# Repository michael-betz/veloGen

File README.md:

# light branch
  * No OLED display support
  * No touch button support
  * velogen PCB is in a waterproof box
  - [ ] Support for RGB LED back-light
  - [ ] Support for GPS module
  - [ ] Support for remote server

# veloGen
Minimalist bike computer and hub dynamo power manager.

A typical hub dynamo can deliver approx. 6 - 10 V at 0.5 A. Output current is inductively limited and stays relatively stable over speed. However voltage will go up. A custom made buck converter is used to extract maximum power and charge a 18650 liion cell. The front and back bike lights will be powered by this cell.

Speed and distance is tracked by measuring the zero crossings of the hub dynamo AC output. Data is collected in the CPU until read out by a mobile device over bluetooth and possibly published to a cloud service.

# Brainstorming

 * Will use ESP-WROOM-32 and make good use of the sleep modes
 * AC input zero crossing --> falling edge interrupt. Wake up CPU and increment counting reg.
 * Every second, keep track of:
   * Battery voltage. --> ADC + voltage divider to 3 V
   * Generator RMS(or peak) voltage. --> ADC + voltage divider to 3 V
   * Generator RMS current. --> 5 mOhm shunt + TS1101 + ADC 1 V
   * Battery current in and out --> 5 mOhm shunt + TS1101 + ADC 1 V
   * Realtime clock timestamp
* Store these datasets in a circular buffer in memory, until read out over BLE.
* Manage the Buck converter PWM to charge the battery with maximum current

## PCB

 * 3.3 V LDO
 * WROOM-32
 * Buck inductor
 * Buck Schottky: STPS3L40UF
 * High side mosfet driver: LTC4440-5 in SOT-23
 * High side Mosfet: STL6N3LLH6
 * 4 x schottky diode for bridge rectifier
 * Smoothing cap (10 uF?)
 * 2 x current sensing shunt (Igenerator, Ibattery) + 2 x TS1101
 * IN system programming pins
 * P - channel mosfet to switch off external power on fault (low battery / overcurrent)

### Datasheets
 * [MCP1630](http://ww1.microchip.com/downloads/en/DeviceDoc/21896b.pdf)
 * [LiIon app note](http://ww1.microchip.com/downloads/en/DeviceDoc/51555b.pdf)

## 3D printed case

 * Mounts with zip ties / verlcro straps on the frame between 2 tubes angeled at 120 deg
 * 2 Shellswhich clip / screw together
 * 5 mm wall thickness with a groove to place an O-ring between the shells
 * AC input cable (2 pin)
 * DC output + I2C cable (4 pin)

# Rev1 Notes
  * Need mounting holes on PCB
  * Case clamping the PCB doesn't work like that
  * Case make teeth tighter
  * Need to find less huge connectors for battery, dynamo and I2C
  * Add OLED to case (Case and PCB can be made wider)

# Bringup (rev1)
  * connect pogo pin adapter to board and USB serial cable
  * force flash voltage to 3.3V

```bash
$ espefuse.py set_flash_voltage 3.3V
espefuse.py v2.7
Connecting........_____....._
Enable internal flash voltage regulator (VDD_SDIO) to 3.3V.
The following efuses are burned: XPD_SDIO_FORCE, XPD_SDIO_REG, XPD_SDIO_TIEH.
This is an irreversible operation.
Type 'BURN' (all capitals) to continue.
BURN
VDD_SDIO setting complete.

$ esptool.py flash_id
esptool.py v2.7
Found 1 serial ports
Serial port /dev/ttyUSB0
Connecting........__
Detecting chip type... ESP32
Chip is ESP32D0WDQ5 (revision 1)
Features: WiFi, BT, Dual Core, 240MHz, VRef calibration in efuse, Coding Scheme None
Crystal is 40MHz
MAC: 40:f5:20:5c:8d:48
Uploading stub...
Running stub...
Stub running...
Manufacturer: c8
Device: 4018
Detected flash size: 16MB
Hard resetting via RTS pin..
```

  * `pio run -t uploadfs`
  * `pio run -t upload -t monitor`

You should see velogen booting up in the terminal.

# Changes to add for REV2

  * add 200k pulldown and 10 nF RC filter to speed sense pin
  * add Zener diode across supply rail
  * real buttons
  * better connectors (waterproofing)
  * Switchable battery power output for front light?
  * Switchable 5 V output for WS2812

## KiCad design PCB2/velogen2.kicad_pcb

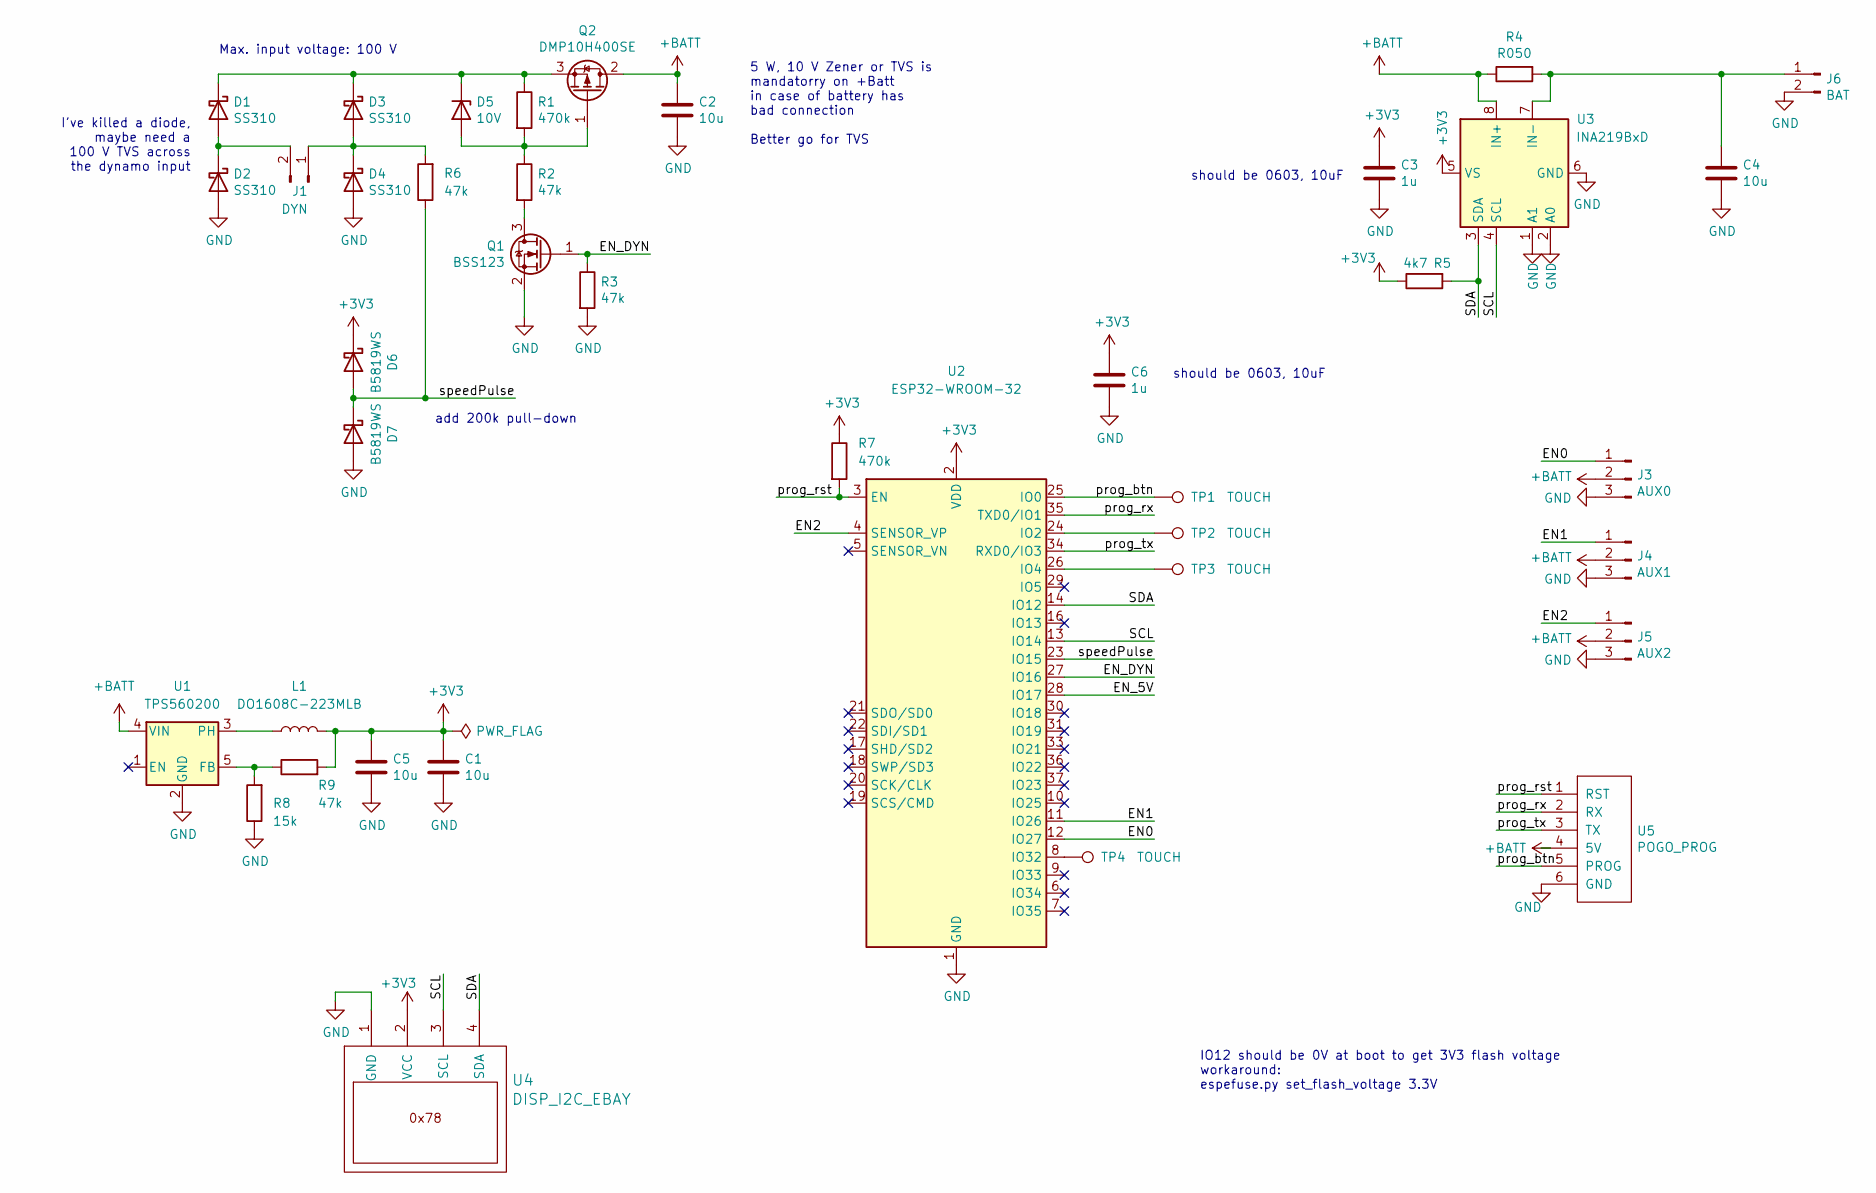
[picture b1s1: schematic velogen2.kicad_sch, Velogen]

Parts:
C1, C5: 10u; C_0603_1608Metric
C2, C4: 10u; C_1210_3225Metric
C3, C6: 1u; C_0805_2012Metric
D1, D2, D3, D4: SS310; D_SMA
D5: 10V; D_SOD-123
D6, D7: B5819WS; D_SOD-323
J1: DYN; JST_XH_S2B-XH-A-1_1x02_P2.50mm_Horizontal
J3: AUX0; JST_XH_S3B-XH-A-1_1x03_P2.50mm_Horizontal
J4: AUX1; JST_XH_S3B-XH-A-1_1x03_P2.50mm_Horizontal
J5: AUX2; JST_XH_S3B-XH-A-1_1x03_P2.50mm_Horizontal
J6: BAT; JST_XH_S2B-XH-A-1_1x02_P2.50mm_Horizontal
L1: DO1608C-223MLB; DO1608
Q1: BSS123; SOT-23
Q2: DMP10H400SE; SOT-223-3_TabPin2
R1, R7: 470k; R_0805_2012Metric
R2, R3, R6, R9: 47k; R_0805_2012Metric
R4: R050; R_1206_3216Metric
R5: 4k7; R_0805_2012Metric
R8: 15k; R_0805_2012Metric
TP1, TP2, TP3, TP4: TOUCH; TestPoint_THTPad_D1.5mm_Drill0.7mm
U1: TPS560200; SOT-23-5
U2: ESP32-WROOM-32
U3: INA219BxD; SOIC-8_3.9x4.9mm_P1.27mm
U4: DISP_I2C_EBAY
U5: POGO_PROG; myPogoPads

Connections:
+3V3: C1.1, C3.1, C5.1, C6.1, D6.1 (K), L1.2, R5.1, R7.1, R9.2, U2.2 (VDD), U3.5 (VS), U4.2 (VCC)
+BATT: C2.1, J3.2, J4.2, J5.2, Q2.2 (D), R4.1, U1.4 (VIN), U3.8 (IN+), U5.4 (5V)
/EN0: J3.1, U2.12 (IO27)
/EN1: J4.1, U2.11 (IO26)
/EN2: J5.1, U2.4 (SENSOR_VP)
/EN_DYN: Q1.1 (G), R3.1, U2.27 (IO16)
/SCL: U2.13 (IO14), U3.4 (SCL), U4.3 (SCL)
/SDA: R5.2, U2.14 (IO12), U3.3 (SDA), U4.4 (SDA)
/prog_btn: TP1.1, U2.25 (IO0), U5.5 (PROG)
/prog_rst: R7.2, U2.3 (EN), U5.1 (RST)
/prog_rx: U2.35 (TXD0/IO1), U5.2 (RX)
/prog_tx: U2.34 (RXD0/IO3), U5.3 (TX)
/speedPulse: D6.2 (A), D7.1 (K), R6.1, U2.23 (IO15)
GND: C1.2, C2.2, C3.2, C4.2, C5.2, C6.2, D2.2 (A), D4.2 (A), D7.2 (A), J3.3, J4.3, J5.3, J6.2, Q1.2 (S), R3.2, R8.1, U1.2 (GND), U2.1 (GND), U2.15 (GND), U2.38 (GND), U2.39 (GND), U3.1 (A1), U3.2 (A0), U3.6 (GND), U4.1 (GND), U5.6 (GND)
unnamed: C4.1, J6.1, R4.2, U3.7 (IN-)
unnamed: D1.1 (K), D3.1 (K), D5.1 (K), Q2.3 (S), R1.1
unnamed: D1.2 (A), D2.1 (K), J1.2
unnamed: D3.2 (A), D4.1 (K), J1.1, R6.2
unnamed: D5.2 (A), Q2.1 (G), R1.2, R2.1
unnamed: L1.1, U1.3 (PH)
unnamed: Q1.3 (D), R2.2
unnamed: R8.2, R9.1, U1.5 (FB)
unnamed: TP2.1, U2.24 (IO2)
unnamed: TP3.1, U2.26 (IO4)
unnamed: TP4.1, U2.8 (IO32)

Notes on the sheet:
IO12 should be 0V at boot to get 3V3 flash voltage workaround: espefuse.py set_flash_voltage 3.3V
add 200k pull-down
5 W, 10 V Zener or TVS is mandatorry on +Batt in case of battery has bad connection Better go for TVS
should be 0603, 10uF
I've killed a diode, maybe need a 100 V TVS across the dynamo input
Max. input voltage: 100 V

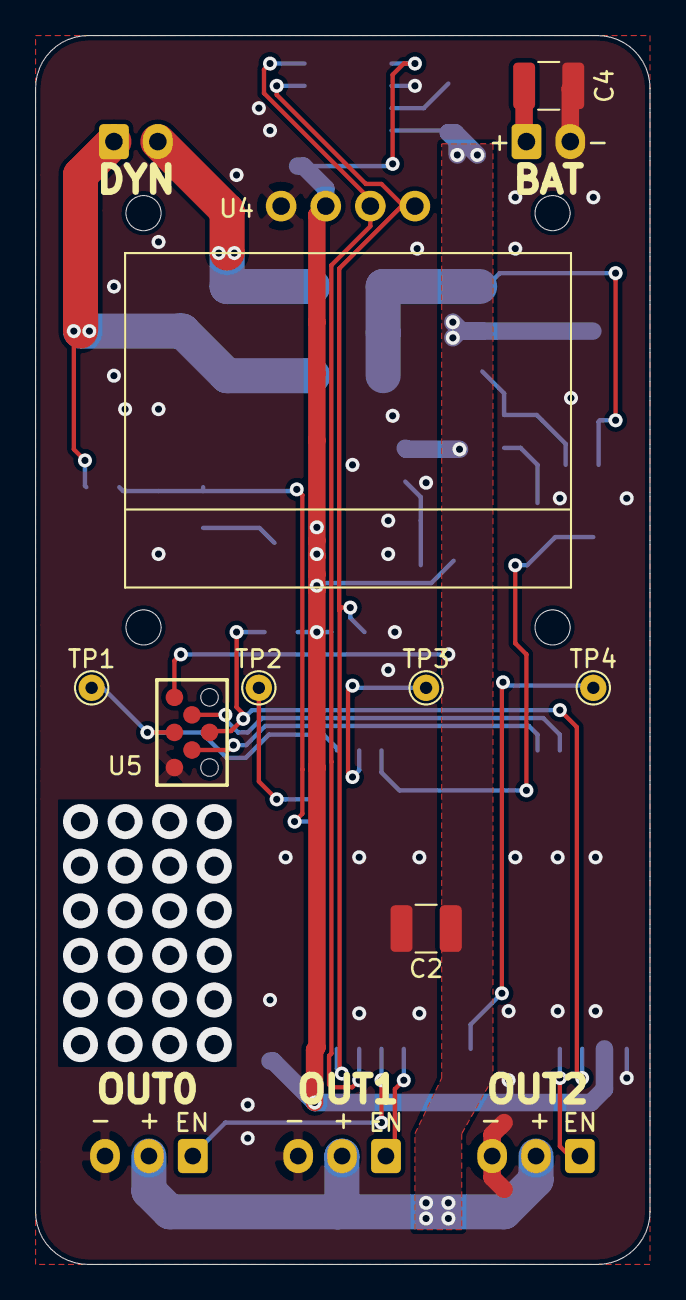
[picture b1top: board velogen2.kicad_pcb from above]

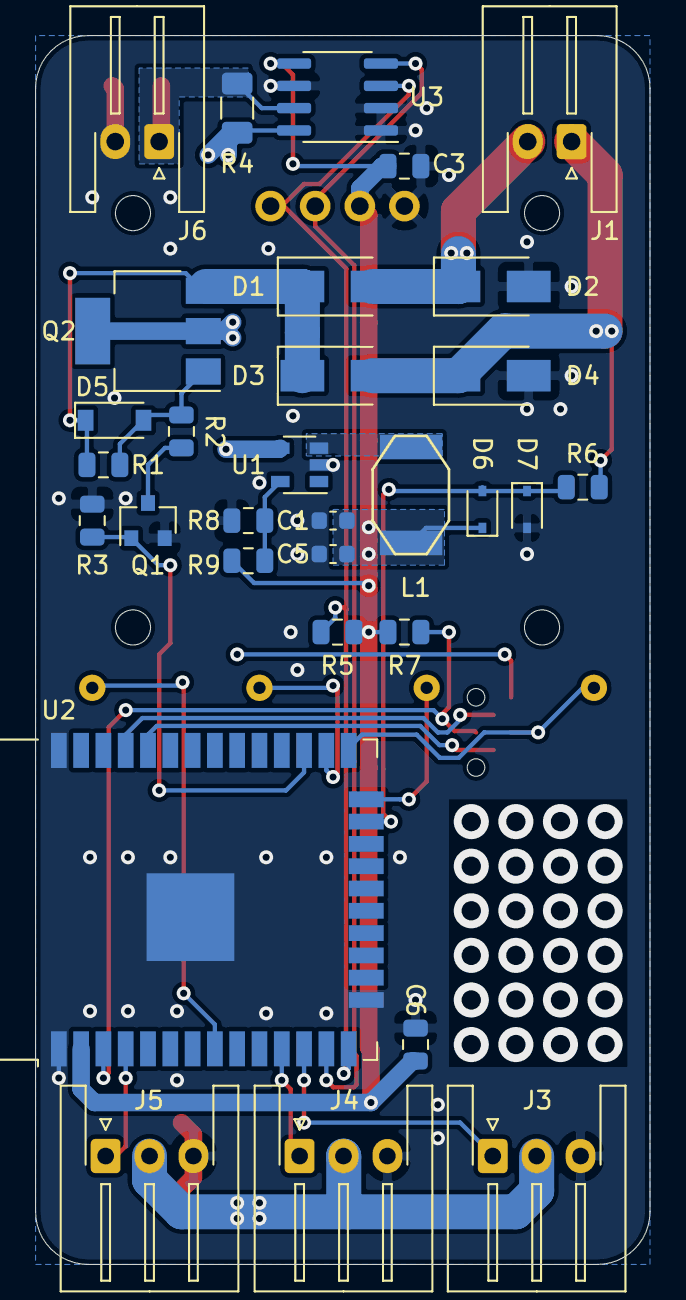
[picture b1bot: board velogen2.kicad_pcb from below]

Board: 2 copper layers, 35.0 x 70.0 mm, 39 parts (31 on the bottom side), 25 nets.

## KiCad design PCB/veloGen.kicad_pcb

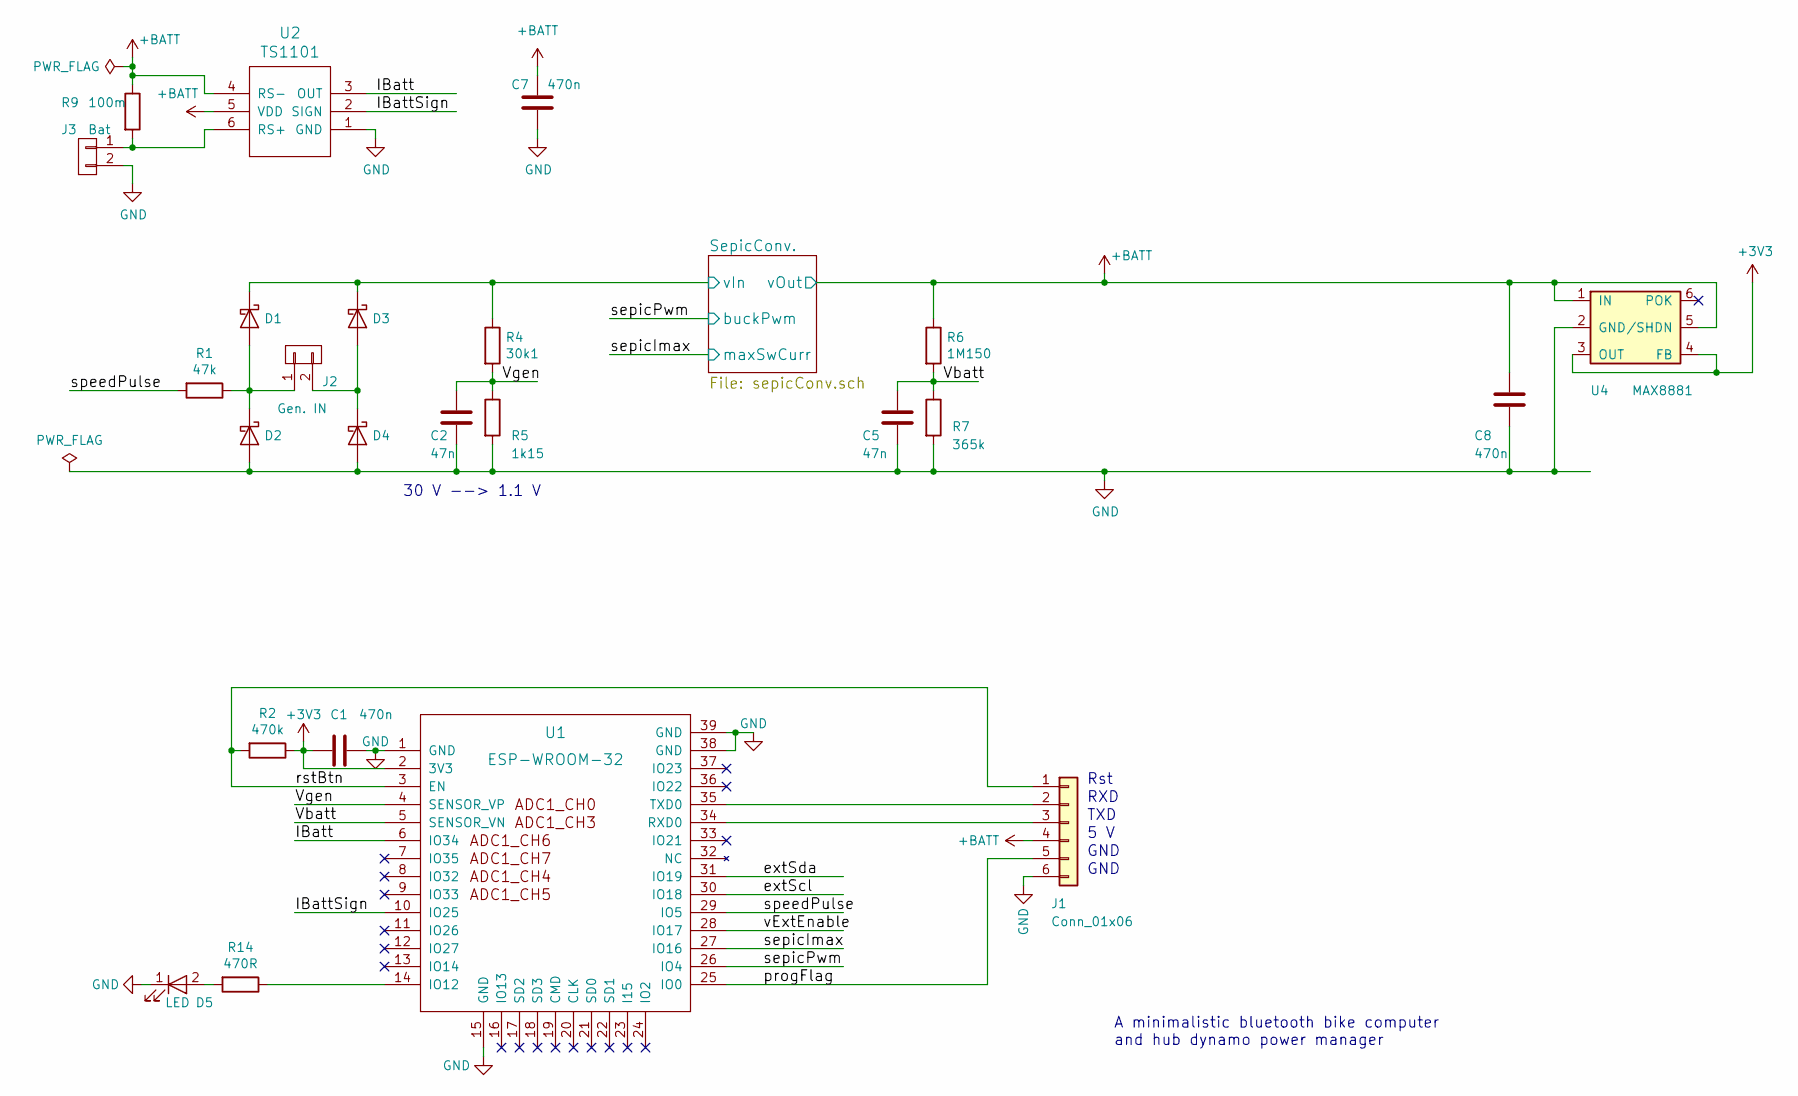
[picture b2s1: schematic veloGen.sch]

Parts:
C1, C7, C8: 470n; C_0805
C2, C5: 47n; C_0805
D1, D2, D3, D4: B5819WS; D_SOD-323
D5: LED; LED_0805
J1: Conn_01x06; myPogoPads
J2: Gen. IN; Pin_Header_Straight_1x02_Pitch2.54mm
J3: Bat; Pin_Header_Straight_1x02_Pitch2.54mm
R1: 47k; R_0805
R2: 470k; R_0805
R4: 30k1; R_0805
R5: 1k15; R_0805
R6: 1M150; R_0805
R7: 365k; R_0805
R9: 100m; R_1206
R14: 470R; R_0805
U1: ESP-WROOM-32
U2: TS1101; SOT-23-6_Handsoldering
U4: MAX8881; SOT-23-6

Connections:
+3V3: C1.2, R2.1, U1.2 (3V3), U4.3 (OUT), U4.4 (FB)
+BATT: C7.1, C8.1, J1.4, R6.1, R9.1, U2.4 (RS-), U2.5 (VDD), U4.1 (IN), U4.5 (/SHDN); also elsewhere on the board
/IBatt: U1.6 (IO34), U2.3 (OUT)
/IBattSign: U1.10 (IO25), U2.2 (SIGN)
/SepicConv./vIn: D1.1 (K), D3.1 (K), R4.1; also elsewhere on the board
/Vbatt: C5.1, R6.2, R7.1, U1.5 (SENSOR_VN)
/Vgen: C2.1, R4.2, R5.1, U1.4 (SENSOR_VP)
/extScl: U1.30 (IO18)
/extSda: U1.31 (IO19)
/progFlag: J1.5, U1.25 (IO0)
/rstBtn: J1.1, R2.2, U1.3 (EN)
/sepicImax: U1.27 (IO16); also elsewhere on the board
/sepicPwm: U1.26 (IO4); also elsewhere on the board
/speedPulse: R1.2, U1.29 (IO5)
/vExtEnable: U1.28 (IO17)
GND: C1.1, C2.2, C5.2, C7.2, C8.2, D2.2 (A), D4.2 (A), D5.1 (K), J1.6, J3.2, R5.2, R7.2, U1.1 (GND), U1.15 (GND), U1.38 (GND), U1.39 (GND), U2.1 (GND), U4.2 (GND); also elsewhere on the board
unnamed: D1.2 (A), D2.1 (K), J2.1, R1.1
unnamed: D3.2 (A), D4.1 (K), J2.2
unnamed: D5.2 (A), R14.2
unnamed: J1.2, U1.35 (TXD0)
unnamed: J1.3, U1.34 (RXD0)
unnamed: J3.1, R9.2, U2.6 (RS+)
unnamed: R14.1, U1.14 (IO12)

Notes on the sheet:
A minimalistic bluetooth bike computer and hub dynamo power manager
30 V --> 1.1 V
Rst
RXD
TXD
5 V
GND

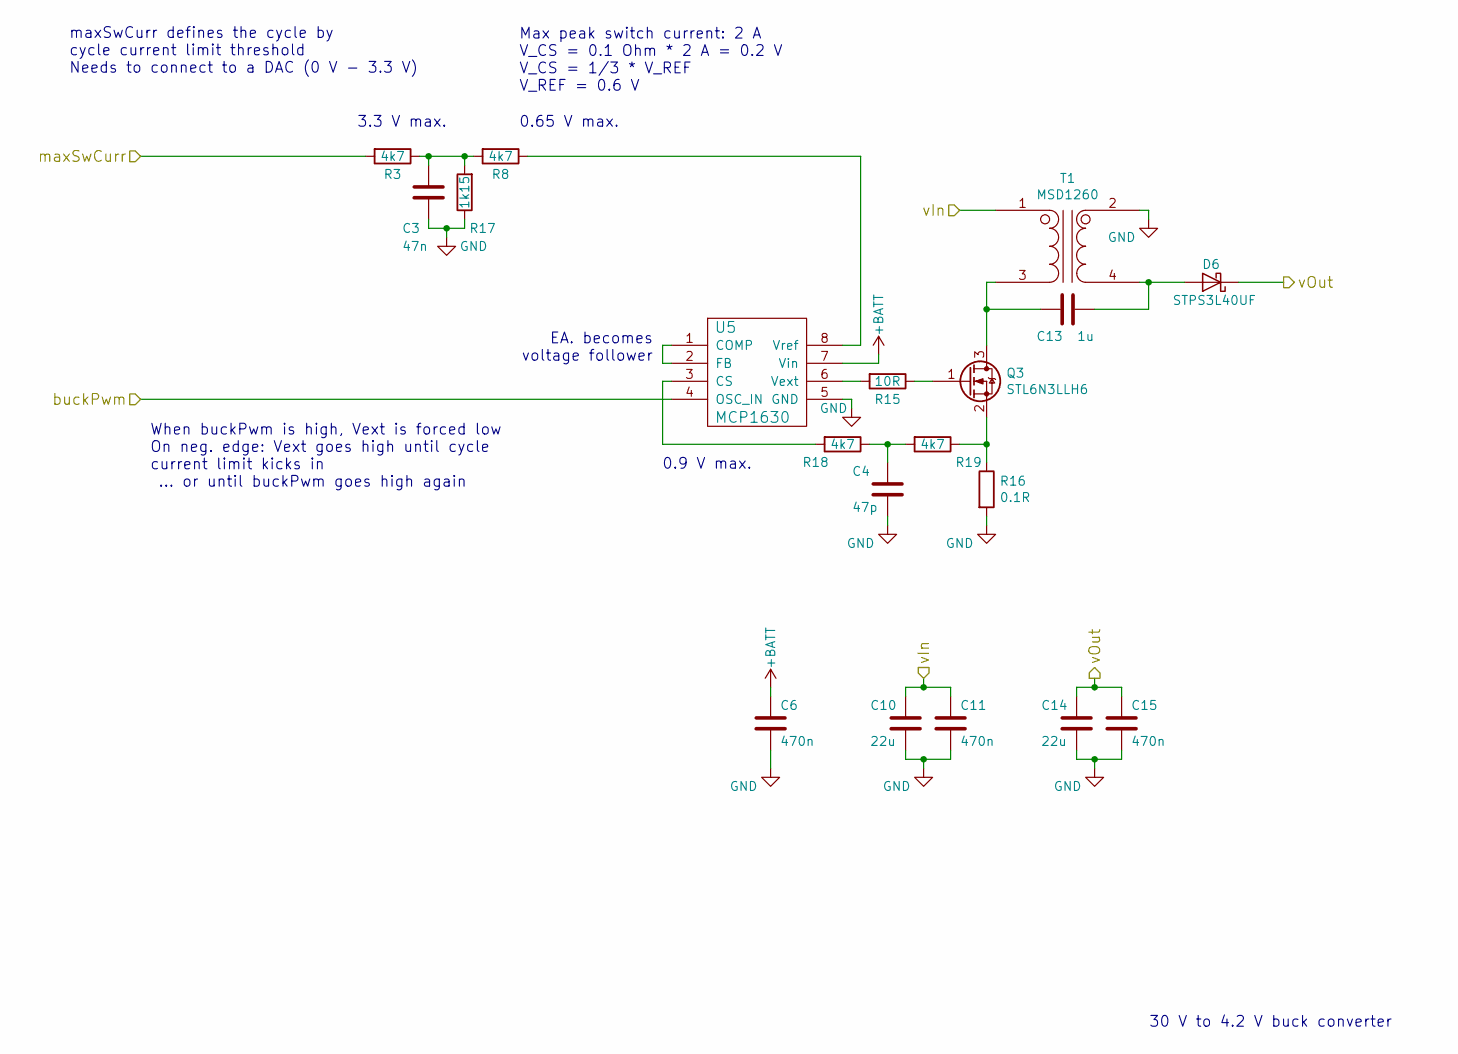
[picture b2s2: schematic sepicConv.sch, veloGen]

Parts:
C3: 47n; C_0805
C4: 47p; C_0805
C6, C11, C15: 470n; C_0805
C10, C14: 22u; C_1206
C13: 1u; C_0805
D6: STPS3L40UF; D_SMB_Standard
Q3: STL6N3LLH6; PowerFLAT_2x2
R3, R8, R18, R19: 4k7; R_0805
R15: 10R; R_0805
R16: 0.1R; R_1206
R17: 1k15; R_0805
T1: MSD1260
U5: MCP1630; MSOP-8_3x3mm_Pitch0.65mm

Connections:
+BATT: C6.2, C14.1, C15.2, D6.1 (K), U5.7 (Vin); also elsewhere on the board
/SepicConv./vIn: C10.1, C11.2, T1.1 (AA); also elsewhere on the board
/sepicImax: R3.2; also elsewhere on the board
/sepicPwm: U5.4 (OSC_IN); also elsewhere on the board
GND: C3.2, C4.2, C6.1, C10.2, C11.1, C14.2, C15.1, R16.2, R17.1, T1.2 (AB), U5.5 (GND); also elsewhere on the board
unnamed: C3.1, R3.1, R8.2, R17.2
unnamed: C4.1, R18.1, R19.2
unnamed: C13.1, D6.2 (A), T1.4 (SB)
unnamed: C13.2, Q3.3 (D), T1.3 (SA)
unnamed: Q3.1 (G), R15.1
unnamed: Q3.2 (S), R16.1, R19.1
unnamed: R8.1, U5.8 (Vref)
unnamed: R15.2, U5.6 (Vext)
unnamed: R18.2, U5.3 (CS)
unnamed: U5.1 (COMP), U5.2 (FB)

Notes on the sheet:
30 V to 4.2 V buck converter
When buckPwm is high, Vext is forced low On neg. edge: Vext goes high until cycle current limit kicks in ... or until buckPwm goes high again
EA. becomes voltage follower
maxSwCurr defines the cycle by cycle current limit threshold Needs to connect to a DAC (0 V - 3.3 V)
0.9 V max.
Max peak switch current: 2 A V_CS = 0.1 Ohm * 2 A = 0.2 V V_CS = 1/3 * V_REF V_REF = 0.6 V
0.65 V max.
3.3 V max.

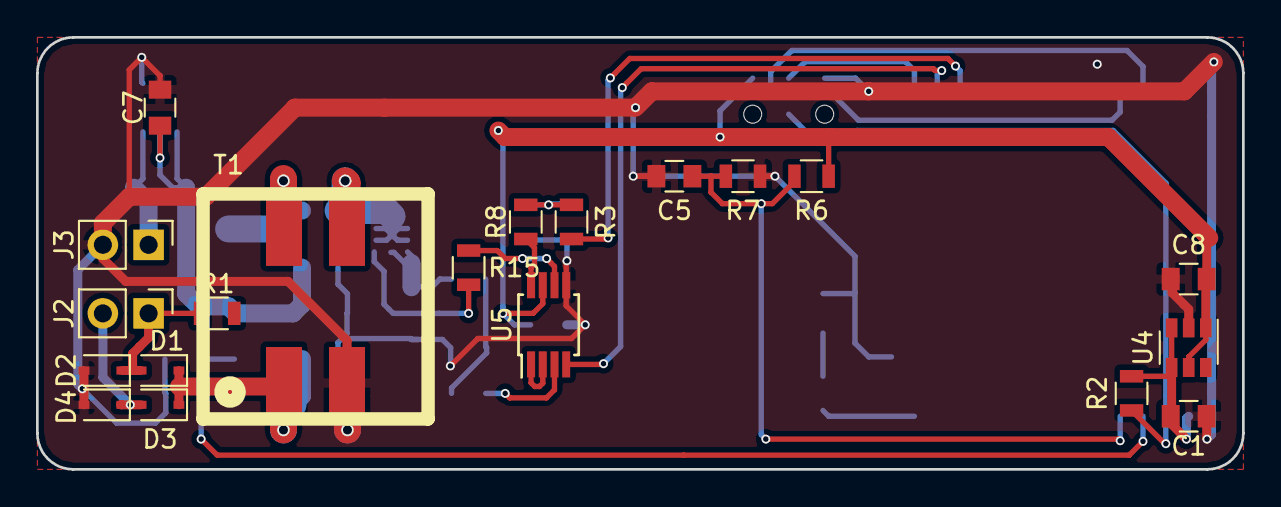
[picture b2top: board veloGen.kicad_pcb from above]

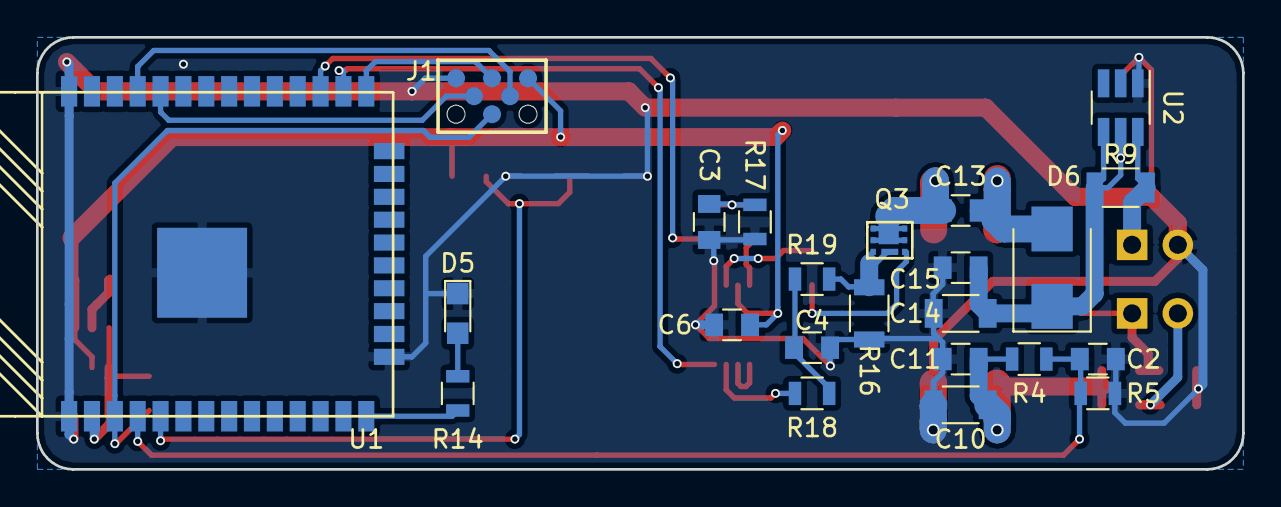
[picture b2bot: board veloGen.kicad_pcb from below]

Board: 2 copper layers, 67.0 x 24.0 mm, 43 parts (23 on the bottom side), 30 nets.

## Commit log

2017-03-18 Started with the Schematic
2017-03-20 Got more specific about parts
2017-03-21 Started the Schematic
2017-03-21 Started real schematic
2017-03-21 Refined the schematic
2017-03-22 Schematic one step closer
2017-03-23 Moved around some components a bit
2017-03-24 Layout ideas
2017-03-29 Added template esp32 project
2017-04-04 80 MHz without WIFI: 26 mA
2017-04-04 cleaned up a bit
2017-04-06 Played around with Hardware PWM
2017-04-07 minor stuff:
2017-04-19 Added SEPIC ltspice model
2017-04-20 Simulation is working (including the cycle by cycle current limit)
2017-05-25 Schematic work
2017-10-04 Simplified schematic and started layout
2017-10-04 Added MQTT controlable mqtt test firmware
2017-10-04 completed an ugly pcb with minimalistic fuctionality
2017-10-05 Added batery current sense
2017-10-06 revised layout
2017-10-07 moved stuff around 0.6 vias
2017-10-09 built first prototype, some mods are needed
2017-10-11 Fixed current measurement
2017-10-17 Fixed the linear calibration factor for VBatt
2017-10-20 Added I-sense cal constants
2017-10-23 Screwed up attempt of an TFTP server. Needs to be changed to be more FreeRTOS style
2017-10-24 Stateless try
2017-10-24 Cleaned up tftp a bit
2017-10-24 tftp builds, timout still missing
2017-10-25 Timeout still missing:
2017-10-25 Went back to statemachine
2017-10-26 states wokr for sending
2017-10-27 Added blocksize option
2017-10-27 tftp almost feature complete
2017-10-28 TFTP client tested and working. TX and RX. Opt and NoOpt
2017-10-28 Fixed some bugs to make curl happy
2017-10-30 Got httpd working
2017-10-31 Bit of a clean up
2017-11-01 Added a web debugging console
2017-11-05 Quite happy with how the web console turned out
2017-11-05 Cleanup
2017-11-06 Added SPIFFS write support through POST
2017-11-06 Some bugs in directory listing
2017-11-07 moved log persistence to RTC memory
2017-11-08 Made GET /log.txt multipart response. Added mV and mA measurement and gauges
2017-11-10 Added spiffs image
2017-11-12 Made wifi connection process a bit smarter
2017-11-13 AP / STA
2017-11-19 stuff
2018-04-06 fun with openscad!
2018-04-09 open-scad is addicting!
2018-08-30 Half shell looks good
2018-08-31 Looking good
2018-08-31 Printed lower shell
2018-09-03 Battery case work
2018-09-04 off to the printer it goes
2018-09-05 kinda works
2019-05-27 First bike test run. Fried the board :(
2019-06-01 new revision on battery holder
2020-09-09 add second stab at velogen PCB
2020-09-09 pcbShell: adapt for larger PCB2 size
2020-09-17 Added Schottkey diode; Clean up ERC
2020-09-17 PCB: Moved R2
2020-09-19 clean up schematic symbols
    * re-associate standard symbols with the standard library (needs to be
    installed)
    * remove `myStuff` library. Symbols from there are now in rescue.lib
    * make the 3V3 enable switch a jumper poking out trough the case
2020-09-19 add symbol cache to gitignore
2020-09-19 move all small components to top side
2020-09-22 sch: fix some component names
2020-09-22 put propper package (SMA) for diodes
2020-09-23 did some routing of the power rails
    * kinda stuck on the 3V3, might need to re-consider placement
2020-09-23 top half is routed
2020-09-28 das Schwein ist bestellt!
2020-10-09 cad: tune the PCB shell, add oled spacer
2020-10-09 add first up code
2020-10-11 work on OLED gui and simulation
2020-10-14 re-structured the micropython code a bit
2020-10-14 add new arduino based firmware
2020-10-15 add touch buttons to switch screens
2020-10-15 move stuff around, crude tachometer works
    ... using floats. Feels like cheating.
2020-10-16 wifi managment
    * add first stab at asynchronous wifi setup / teardown
    still needs some polishing :p
2020-10-18 last version using arduino
2020-10-18 clean up and move things around a bit
2020-10-18 add new ESP_IDF based firmware, move things around
2020-10-19 first test with MQTT + SSL
    * add jupyter notebook with some number crunching experiments
2020-10-20 update plots
2020-10-20 mqtt caching seems to work reasonably well
    * push measurements over mqtt qos1 when connected
    * otherwise write them to a file in NVM and dump the file over mqtt
    when connected
    * 1 measurement = 16 bytes chunk. 1 mqtt message has N >= 1 chunks.
    binary encoded
    * measurements may arrive out of order / duplicated, server needs to
2020-10-20 some mqtt polishing
2020-10-21 add OTA functionality
    * add self-signed certificates for developing on local network
    * add script to start local https server
    * add OTA screen to trigger the update
    * make lv_update_label() behave like printf
2020-10-21 add settings.json editor over http
    * this version uses GET and POST instead of a websocket
2020-10-21 add UDP logging
    * log output is forwarded to a local IP addr
    * also add hack to get the new websocket features of esp_http_server
    (but not used yet)
2020-10-22 remove self signed certificates
    * use certs/gen_certs.sh to generate your own!
2020-10-22 fix reboot issue
    * had to disconnect wifi before the soft reboot
    * add git describe tag to OTA screen
2020-10-22 add default_settings.json with default values
2020-10-23 proper cicular ring buffer for cache
    * oldest measurements are sent over mqtt first
    * pointers are kept in separate file (maybe faster than having to seek
    to the file header all the time)
    * there's a maximum buffer size, going above that oldest entries will
    be overwritten
2020-10-24 add font-awesome icons + font generation script
    * make measurement rate configurable
    * randomly invert display on boot to mitigate oled burn-in
    * fix off by one bug in fillRect()
2020-10-25 blow cache file size up with dummy bytes
    ... if it is smaller than the write pointer.
    That's because spiffs does not support seeking beyond the end of the
    file.
2020-10-26 add veloServer which dumps data from mqtt to .csv
2020-10-28 add veloPlot.py to plot .csv files more easily
2020-10-29 mqtt_cache.c: reliability improvement
    * 2 alternating files to keep the offset pointers
    * if one gets corrupted on write, use the other
    * prevents loosing the complete cache on reconnect after a power cut
    * enable dynamo by default on powerup
2020-10-29 fix dynamo status on startup
2020-11-12 add IP address to OTA screen
2020-11-13 invert wakeup pin polarity
2020-11-13 fix 2 C warnings
2020-11-13 add oled_rotate_180 setting to .json
2020-11-13 also flip buttons when OLED is rotated
2020-11-13 make button flip work
2020-11-14 update startVeloServer.sh
    which now starts a screen session in the background
2021-09-26 upper_shell: add more clearance for OLED solder pins
2021-09-26 update esp-idf
    * add bringup notes to readme
    * add atexit to velosrver
2021-09-26 add `target_add_binary_data` to CMakeLists.txt
2021-09-26 add `setDynamo()` function
2022-03-06 experimenting with LED strips
    disabled MQTT and FLASH chaching for now
2022-07-22 make mqtt work again, fix nasty bug in LED strip code
2022-07-22 add influxdb2 based velo_server2.py
2022-07-22 fix start_velo_server.sh
2022-07-22 fix screen logging
2022-07-23 add user/pw args
2022-07-24 velo_server: add speed
2022-07-24 verify mqtt with incremental cnt numbers
    * also send speed directly
2022-07-26 mqtt_cache 💣
2022-07-28 attempt to fix the speed reading, untested
2022-07-29 update veloServer, add http ota
2022-07-29 fix km/h on oled
2022-07-29 fix the freaking touch buttons
2024-01-25 port to espressif32@6.5.0
    * compiles, no errors
    * some warnings
    * not tested yet
2024-01-25 fix flash size and partition table
2024-01-28 add some missing files which I forgot to checkin before
2024-01-28 replace ws2812 SPI driver with a RMT one
    also fix some depracated warnings.
    Not tested yet.
2024-01-28 remove unused hacks
2024-01-29 use espressif led-strip library, make it work
    need 24k resistor and 10 nF to ground on speed_sense pin
2024-01-30 led pattern update
2024-01-30 add notes
2024-01-30 better RGB
2024-01-31 add light on / off control depending on time
2024-01-31 make light-off hours configurable, add second animation mode
2024-01-31 speed dependent blink pattern
2024-01-31 tune led animation
2026-05-29 spring cleaning, clang-format
2026-05-29 make it compile
    switch to new I2C API
2026-05-29 led strip on EN1
2026-05-29 runs without crashing
2026-05-29 add button support
2026-05-30 match up with esp_crt wifi stack. Add GPS support.
2026-05-31 much more robust wifi and web-interface
2026-05-31 fix .html of web-interface. remove watchdog
2026-05-31 settings: put log level back
2026-05-31 show some status via the color of the back-light
2026-06-01 rewrote the MQTT cache
2026-06-02 test mqtt on hw
2026-06-02 test on hardware
2026-06-03 add OTA feature. Fix mqtt crash on json reload.
2026-06-03 add OTA task and animation
2026-06-03 add PNP switch to GPS module. deep sleep current went from 2 mA to 0.2 mA
2026-06-04 construct mqtt_topic from hostname
2026-06-04 make g_wheelCnt persistent and reset-able over .json
    also improve json loading without restarting
2026-06-04 optimize struct, reduce ota priority
2026-06-04 add back NTP client
    ... it's usefual after a power cut
2026-06-04 rename some variables
2026-06-05 mqtt: send diff_cnt instead of cnt
2026-06-07 add gps-debug option to forward UART over TCP socket
    this allows to connect with u-center to the GPS module
